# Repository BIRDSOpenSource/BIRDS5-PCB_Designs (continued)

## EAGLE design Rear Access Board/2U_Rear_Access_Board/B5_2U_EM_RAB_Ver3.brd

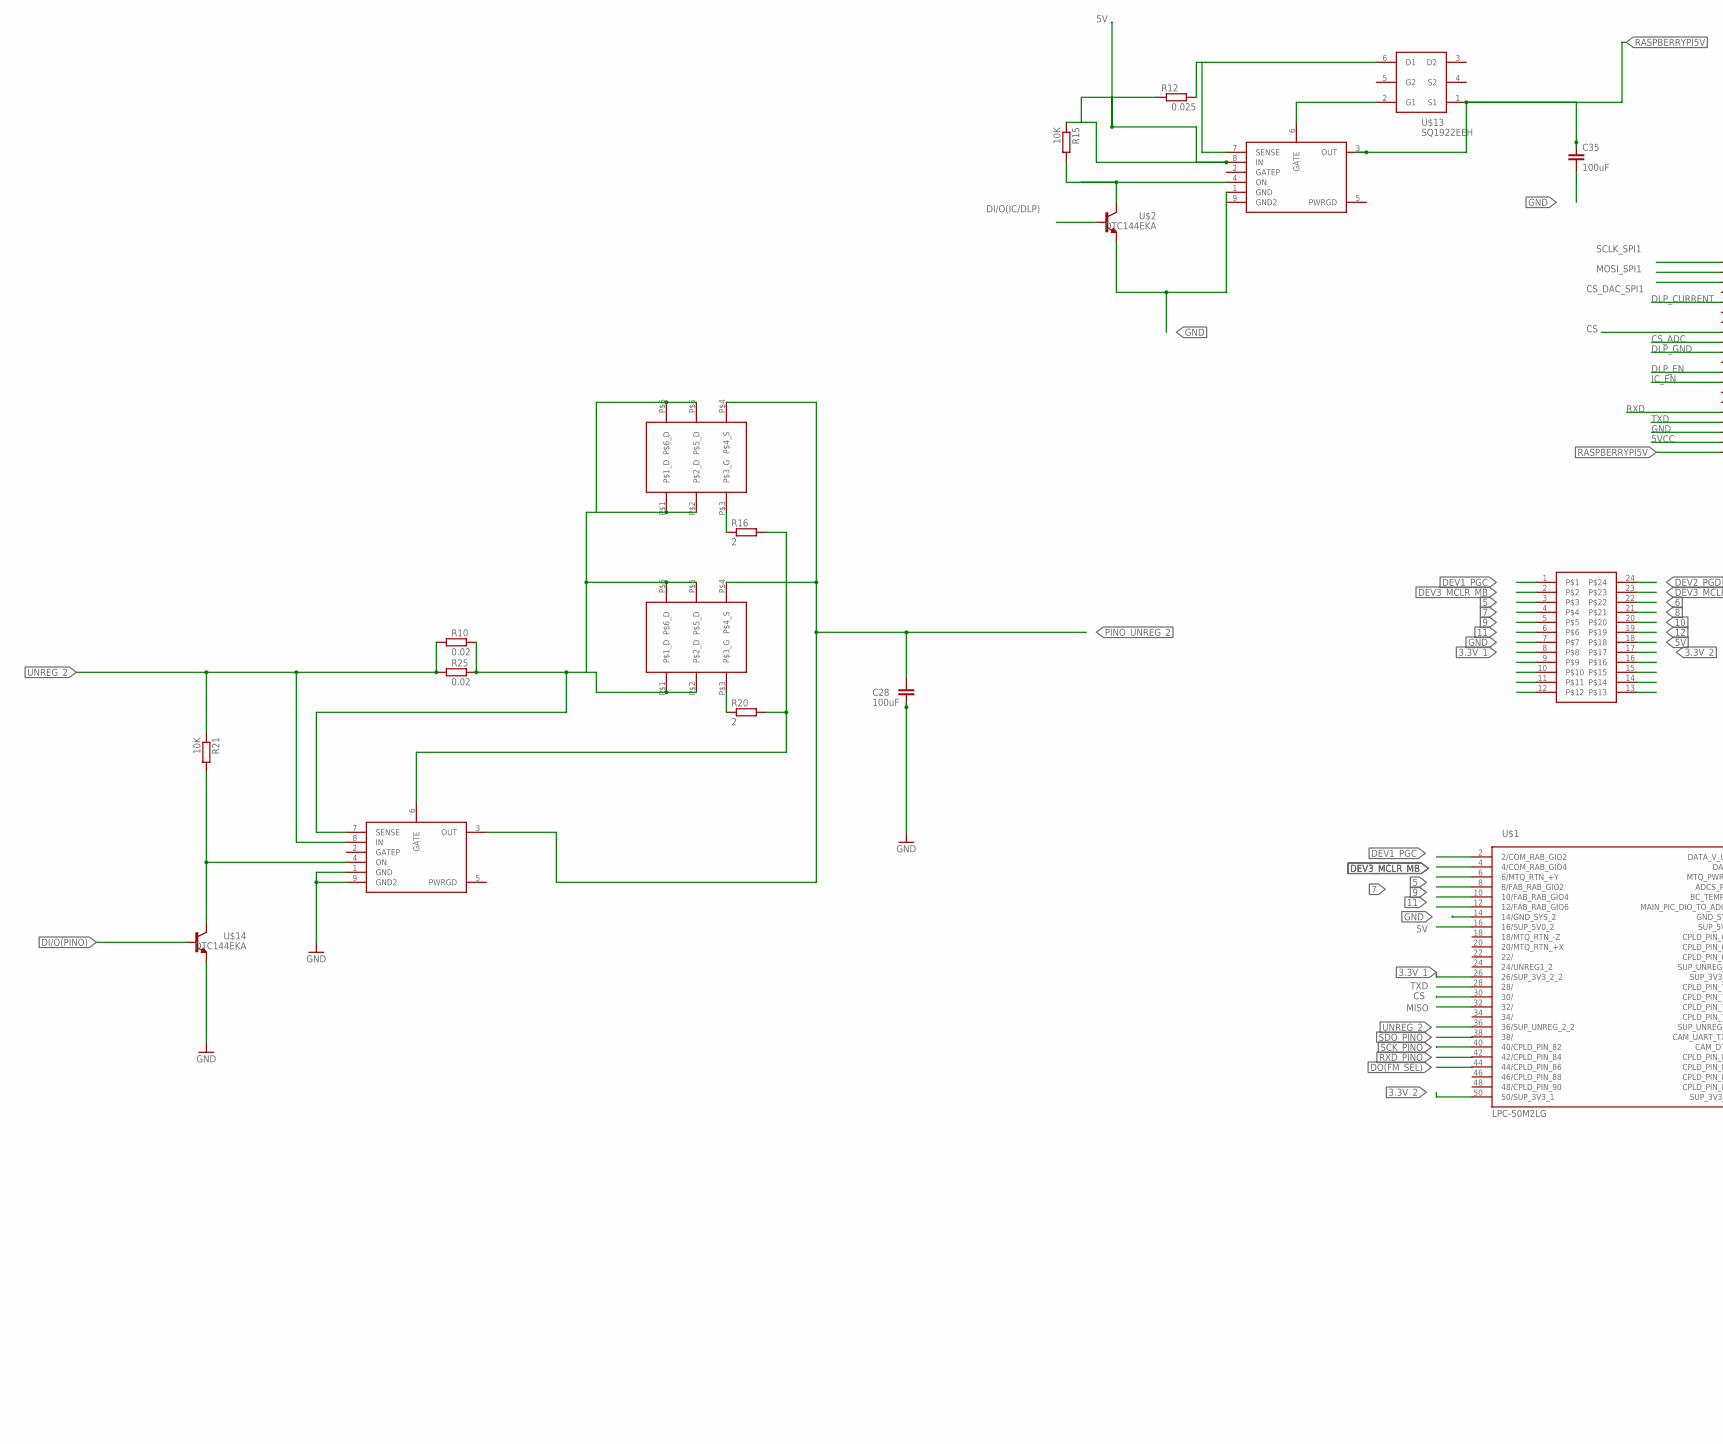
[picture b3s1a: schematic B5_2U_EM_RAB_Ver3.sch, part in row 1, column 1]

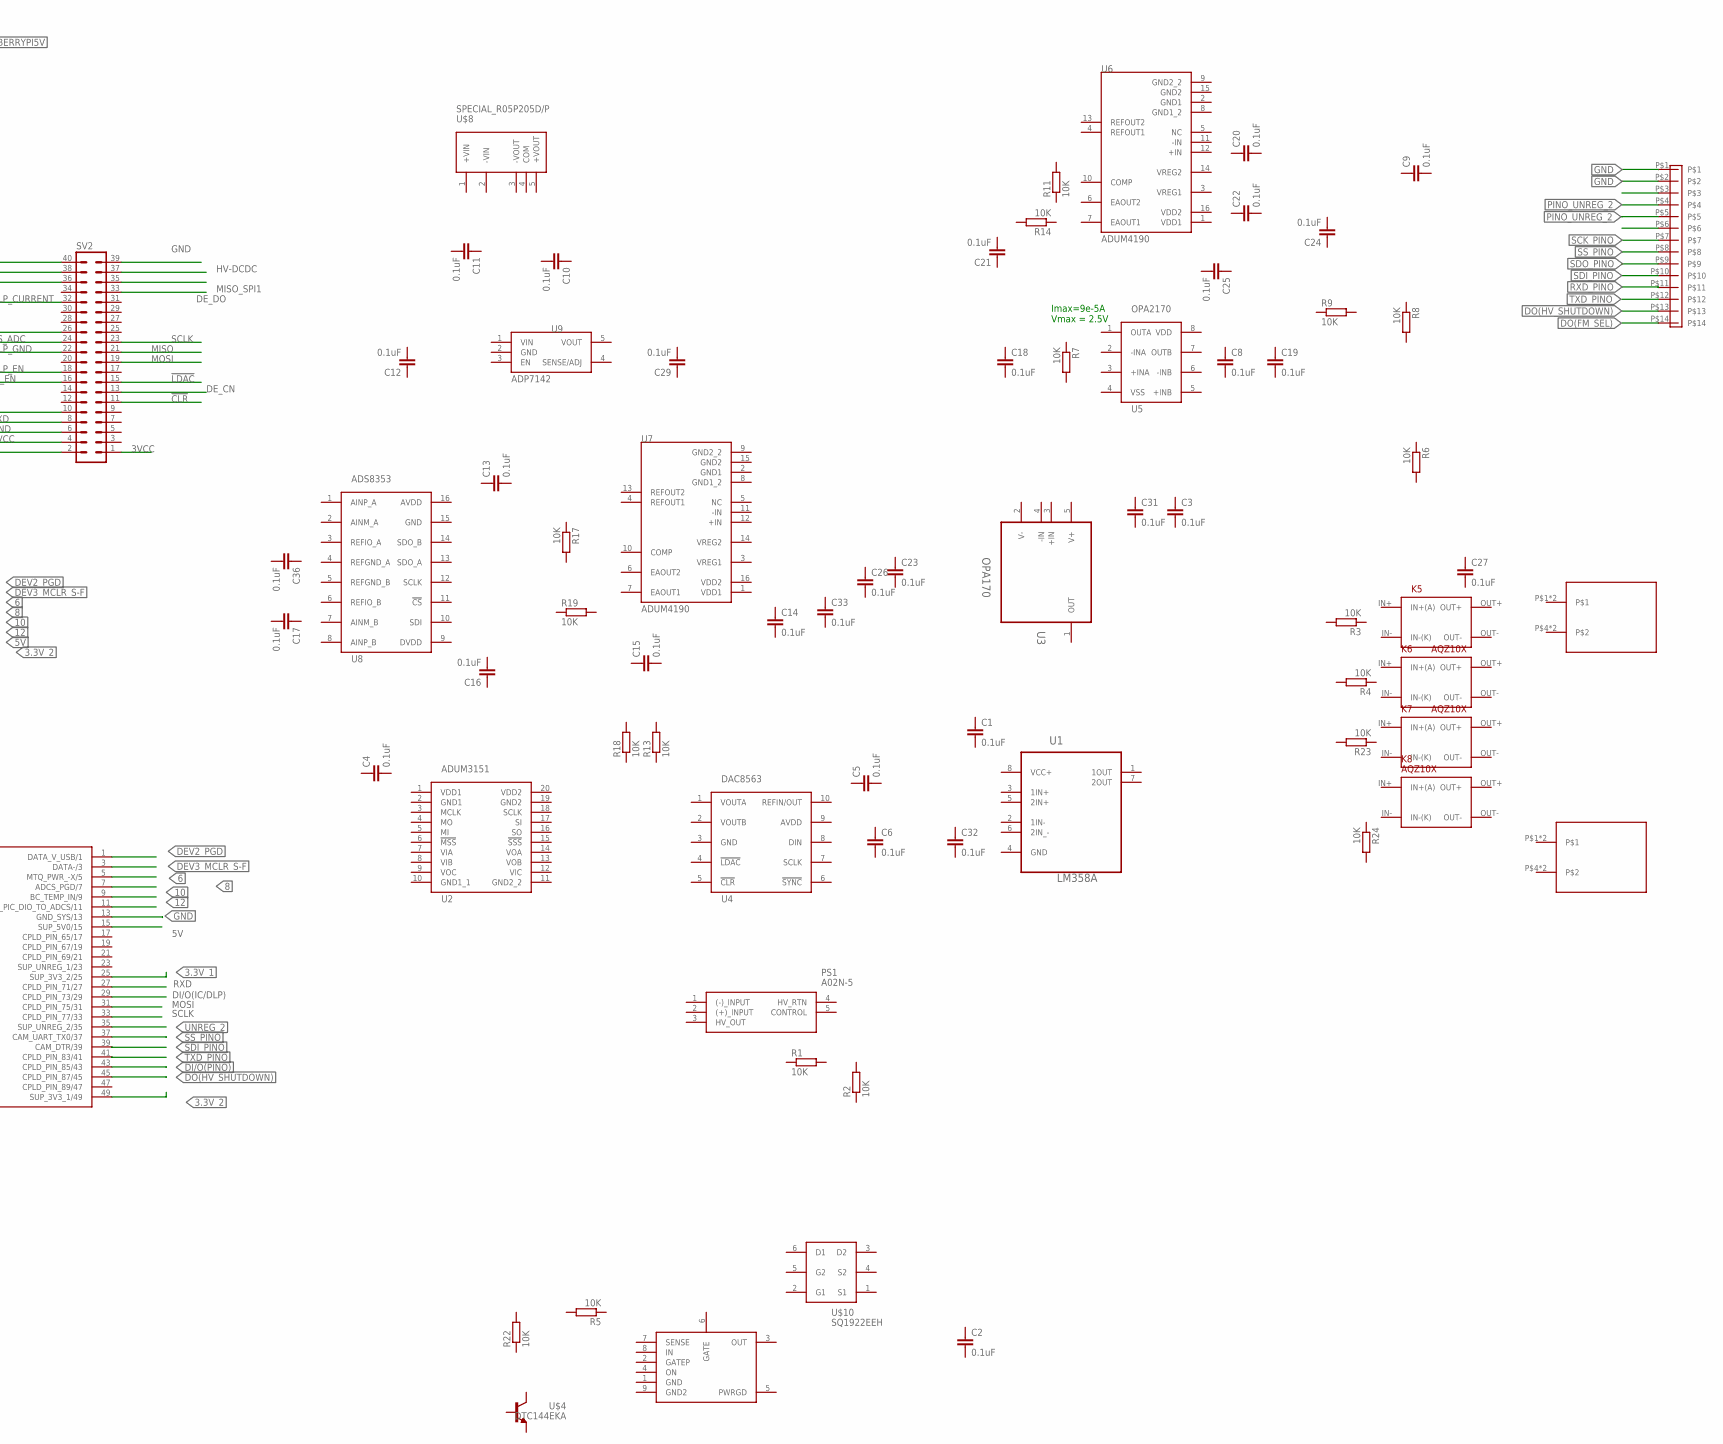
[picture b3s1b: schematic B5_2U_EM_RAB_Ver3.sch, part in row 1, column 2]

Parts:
C1, C2, C3, C4, C5, C6, C8, C9, C10, C11, C12, C13, C14, C15, C16, C17, C18, C19, C20, C21, C22, C23, C24, C25, C26, C27, C29, C31, C32, C33, C36: 0.1uF; C1005
C28: 100uF; C0603
C35: 100uF; C0805
K5, K6, K7, K8: AQZ10X
PS1: A02N-5; A02N5
R1, R2, R3, R4, R5, R6, R7, R8, R9, R11, R13, R14, R15, R17, R18, R19, R21, R22, R23, R24: 10K; R1005
R10, R25: 0.02; R2512
R12: 0.025; R0805
R16, R20: 2; R1005
SV2: MA20-2
U1: LM358A; SOP65P490X110-8N
U2: ADUM3151; SOP65P780X200-20N
U3: OPA170; SOT95P280X145-5N
U4: DAC8563; SOP50P490X110-10N
U5: OPA2170; R-PDSO-G8
U6, U7: ADUM4190; SOIC-16_RI-16-12
U8: ADS8353; SOP65P640X120-16N
U9: ADP7142; SOT95P280X100-5N
U$1: LPC-50M2LG
U$2, U$4, U$14: DTC144EKA; BIRDS3_CAM_MSN_SOT346-R
U$3: RAB_CONECTOR; HDRVR24W40P127_2X12_1564X310X455B
U$5: B14B-PASK-1
U$6, U$11, U$12: BIRDS5_LTC4361
U$7, U$9: DF61_DF61; DF61_DF61Y
U$8: SPECIAL_R05P205D/P
U$10, U$13: SQ1922EEH; BIRDS3_CAM_MSN_SOT65P210X110-6N
U$15, U$16: SSM6K411TU

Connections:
3.3V_1: U$1.25 (SUP_3V3_2/25), U$1.26 (26/SUP_3V3_2_2), U$3.8
3.3V_2: U$1.49 (SUP_3V3_1/49), U$1.50 (50/SUP_3V3_1), U$3.17
3VCC: SV2.1
5: U$1.6 (6/MTQ_RTN_+Y), U$3.3
5V: R12.1, R15.1, U$1.15 (SUP_5V0/15), U$1.16 (16/SUP_5V0_2), U$3.18, U$6.8 (IN)
5VCC: SV2.4
6: U$1.5 (MTQ_PWR_-X/5), U$3.22
7: U$1.8 (8/FAB_RAB_GIO2), U$3.4
8: U$1.7 (ADCS_PGD/7), U$3.21
9: U$1.10 (10/FAB_RAB_GIO4), U$3.5
10: U$1.9 (BC_TEMP_IN/9), U$3.20
11: U$1.12 (12/FAB_RAB_GIO6), U$3.6
12: U$1.11 (MAIN_PIC_DIO_TO_ADCS/11), U$3.19
!CLR: SV2.11
!LDAC: SV2.15
CS: SV2.26, U$1.30 (30/)
CS_ADC: SV2.24
CS_DAC_SPI1: SV2.36
DEV1_PGC: U$1.2 (2/COM_RAB_GIO2), U$3.1
DEV2_PGD: U$1.1 (DATA_V_USB/1), U$3.24
DEV3_MCLR_MB: U$1.4 (4/COM_RAB_GIO4), U$3.2
DEV3_MCLR_S-F: U$1.3 (DATA-/3), U$3.23
DE_CN: SV2.13
DE_DO: SV2.33
DI/O(IC/DLP): U$1.29 (CPLD_PIN_73/29), U$2.2 (B)
DI/O(PINO): U$1.43 (CPLD_PIN_85/43), U$14.2 (B)
DLP_CURRENT: SV2.32
DLP_EN: SV2.18
DLP_GND: SV2.22
DO(FM_SEL): U$1.44 (44/CPLD_PIN_86), U$5.P$14
DO(HV_SHUTDOWN): U$1.45 (CPLD_PIN_87/45), U$5.P$13
GND: C28.2, C35.2, SV2.6, SV2.39, U$1.13 (GND_SYS/13), U$1.14 (14/GND_SYS_2), U$2.1 (E), U$3.7, U$5.P$1, U$5.P$2, U$6.1 (GND), U$6.9 (GND2), U$12.1 (GND), U$12.9 (GND2), U$14.1 (E)
HV-DCDC: SV2.37
IC_EN: SV2.16
MISO: SV2.21, U$1.32 (32/)
MISO_SPI1: SV2.35
MOSI: SV2.19, U$1.31 (CPLD_PIN_75/31)
MOSI_SPI1: SV2.38
unnamed: R20.1, U$15.P$3 (P$3_G)
unnamed: R16.1, U$16.P$3 (P$3_G)
unnamed: R10.2, R25.2, U$12.7 (SENSE), U$15.P$1 (P$1_D), U$15.P$2 (P$2_D), U$15.P$5 (P$5_D), U$15.P$6 (P$6_D), U$16.P$1 (P$1_D), U$16.P$2 (P$2_D), U$16.P$5 (P$5_D), U$16.P$6 (P$6_D)
unnamed: R15.2, U$2.3 (C), U$6.4 (ON)
unnamed: R12.2, U$6.7 (SENSE), U$13.6 (D1)
unnamed: U$6.6 (GATE), U$13.2 (G1)
unnamed: R21.2, U$12.4 (ON), U$14.3 (C)
unnamed: R16.2, R20.2, U$12.6 (GATE)
PINO_UNREG_2: C28.1, U$5.P$4, U$5.P$5, U$12.3 (OUT), U$15.P$4 (P$4_S), U$16.P$4 (P$4_S)
RASPBERRYPI5V: C35.1, SV2.2, U$6.3 (OUT), U$13.1 (S1)
RXD: SV2.10, U$1.27 (CPLD_PIN_71/27)
RXD_PINO: U$1.42 (42/CPLD_PIN_84), U$5.P$11
SCK_PINO: U$1.40 (40/CPLD_PIN_82), U$5.P$7
SCLK: SV2.23, U$1.33 (CPLD_PIN_77/33)
SCLK_SPI1: SV2.40
SDI_PINO: U$1.39 (CAM_DTR/39), U$5.P$10
SDO_PINO: U$1.38 (38/), U$5.P$9
SS_PINO: U$1.37 (CAM_UART_TX0/37), U$5.P$8
TXD: SV2.8, U$1.28 (28/)
TXD_PINO: U$1.41 (CPLD_PIN_83/41), U$5.P$12
UNREG_2: R10.1, R21.1, R25.1, U$1.35 (SUP_UNREG_2/35), U$1.36 (36/SUP_UNREG_2_2), U$12.8 (IN)
V+: U3.5 (V+)
VCC+: U1.8 (VCC+)

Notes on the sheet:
Imax=9e-5A Vmax = 2.5V

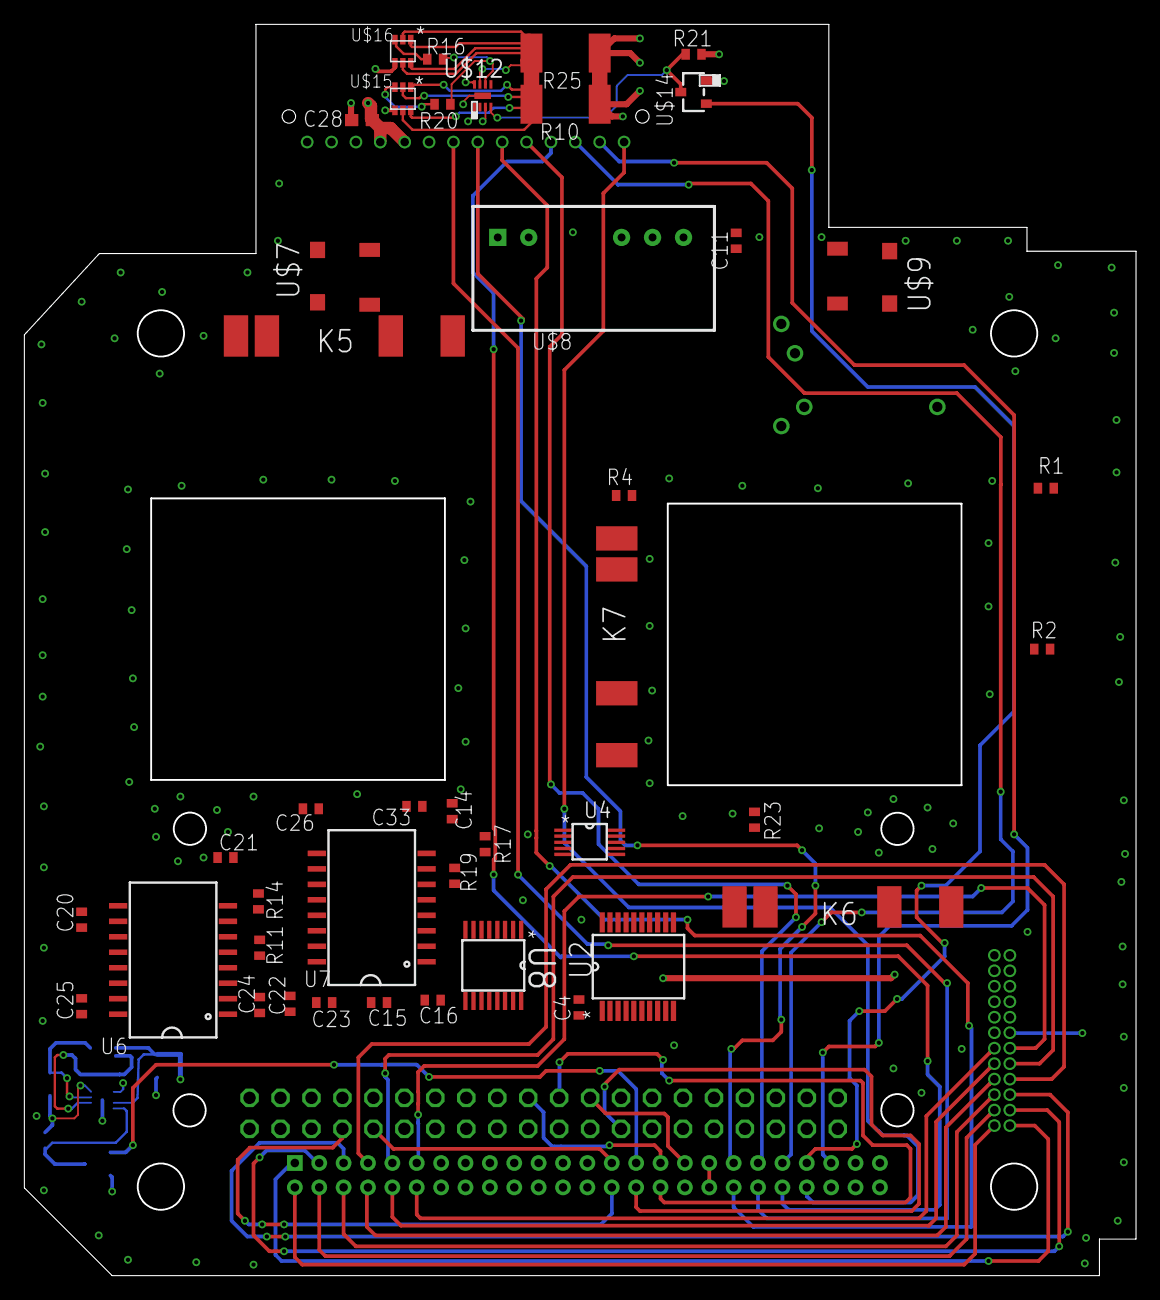
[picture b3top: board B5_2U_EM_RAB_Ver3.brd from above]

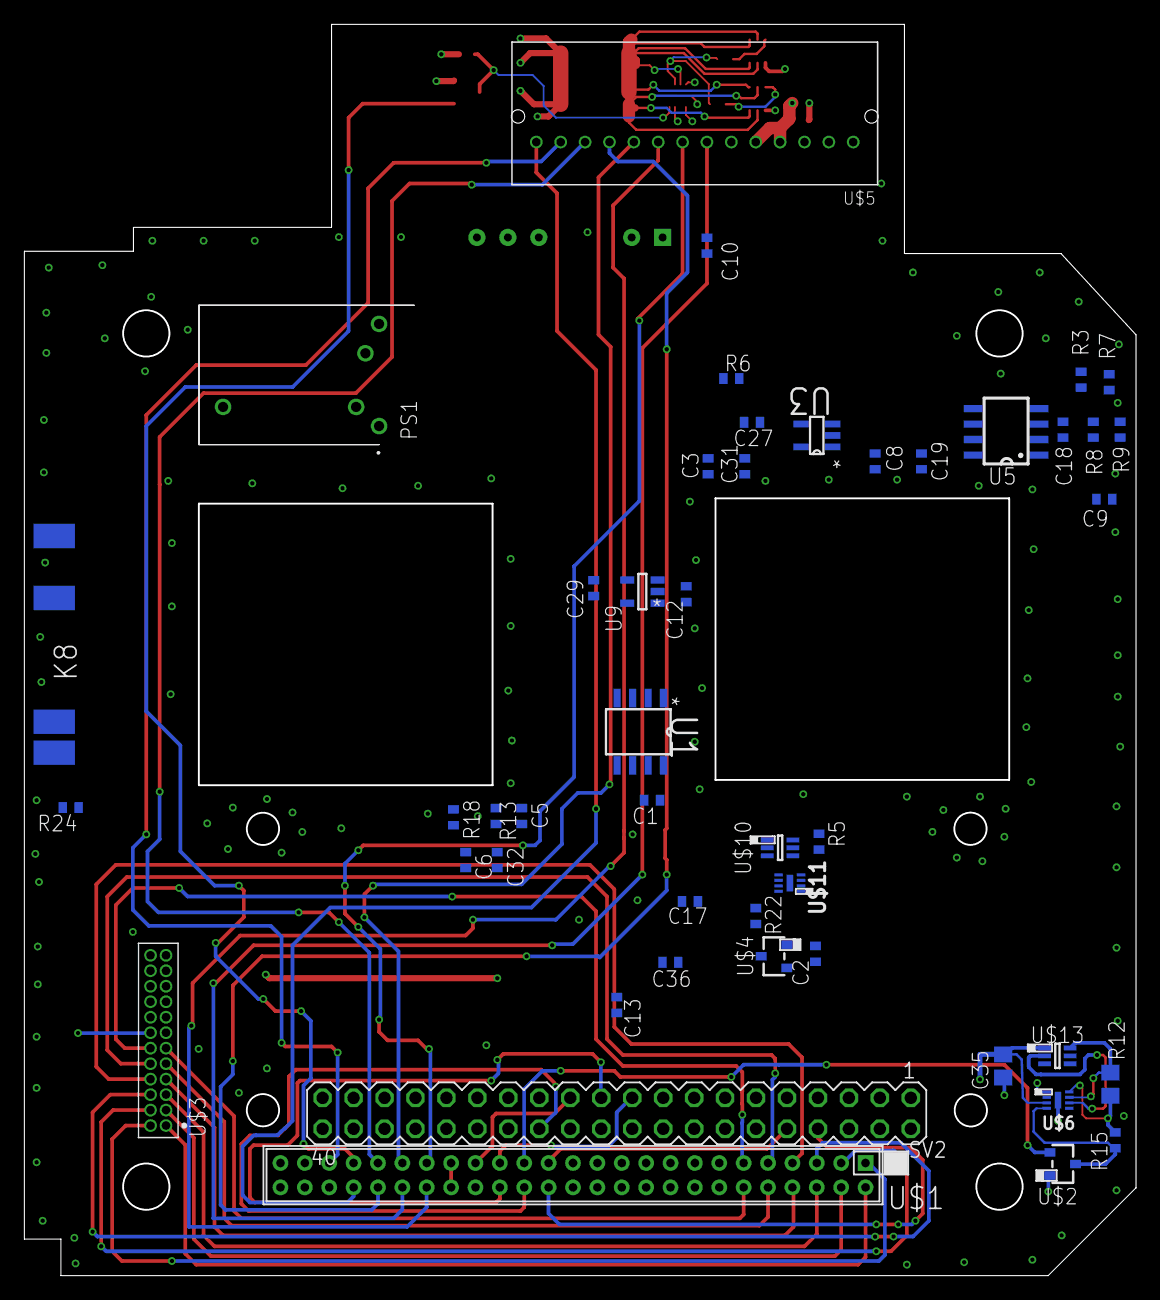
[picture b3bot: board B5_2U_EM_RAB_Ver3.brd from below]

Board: 4 copper layers, 91.2 x 102.7 mm, 89 parts (46 on the bottom side), 43 nets.

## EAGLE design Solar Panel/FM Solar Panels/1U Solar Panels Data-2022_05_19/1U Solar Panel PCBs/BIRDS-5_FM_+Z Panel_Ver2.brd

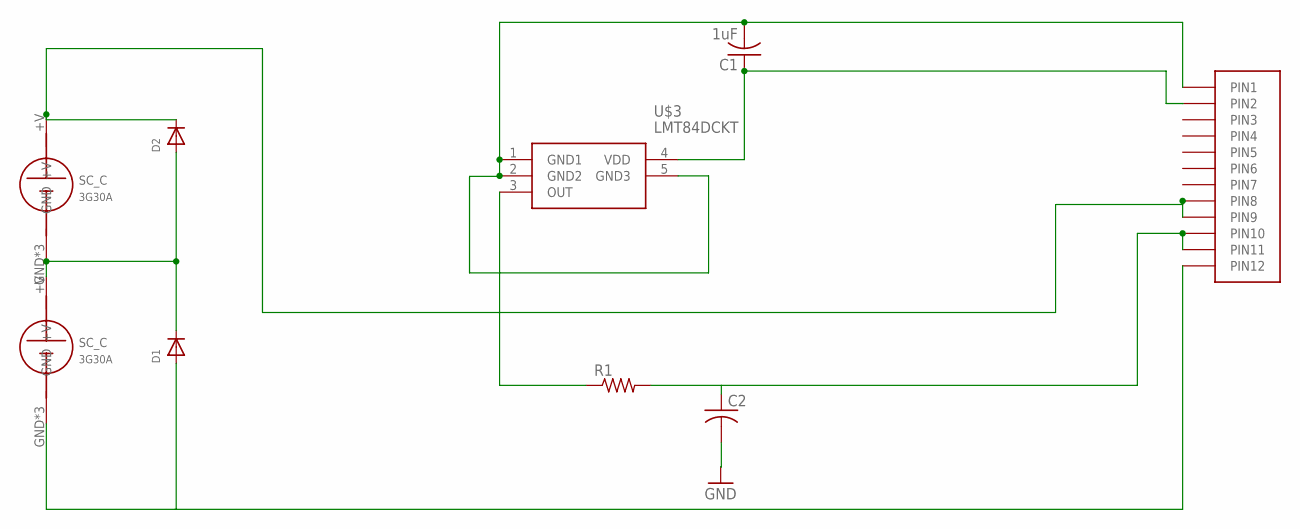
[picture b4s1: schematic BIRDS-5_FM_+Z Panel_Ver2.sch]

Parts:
C1: 1uF; C2012
C2: C-USC2012; C2012
D1, D2: DIODE_SOD-123FL; SOD-123FL
R1: R-US_R0402; R0402
U$1: HEADER12PIN
U$3: LMT84DCKT; SOT65P210X110-5N
U$4, U$5: SC_C

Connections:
+V: D2.C, U$1.P8 (PIN8), U$1.P9 (PIN9), U$4.+V
+VB: D1.C, D2.A, U$4.GND, U$4.GND1 (GND), U$4.GND2 (GND), U$5.+V
GND: C1.2, C2.2, D1.A, U$1.P1 (PIN1), U$1.P12 (PIN12), U$3.1 (GND1), U$3.2 (GND2), U$3.5 (GND3), U$5.GND, U$5.GND1 (GND), U$5.GND2 (GND)
unnamed: C1.1, U$1.P2 (PIN2), U$3.4 (VDD)
unnamed: R1.1, U$3.3 (OUT)
unnamed: C2.1, R1.2, U$1.P10 (PIN10), U$1.P11 (PIN11)

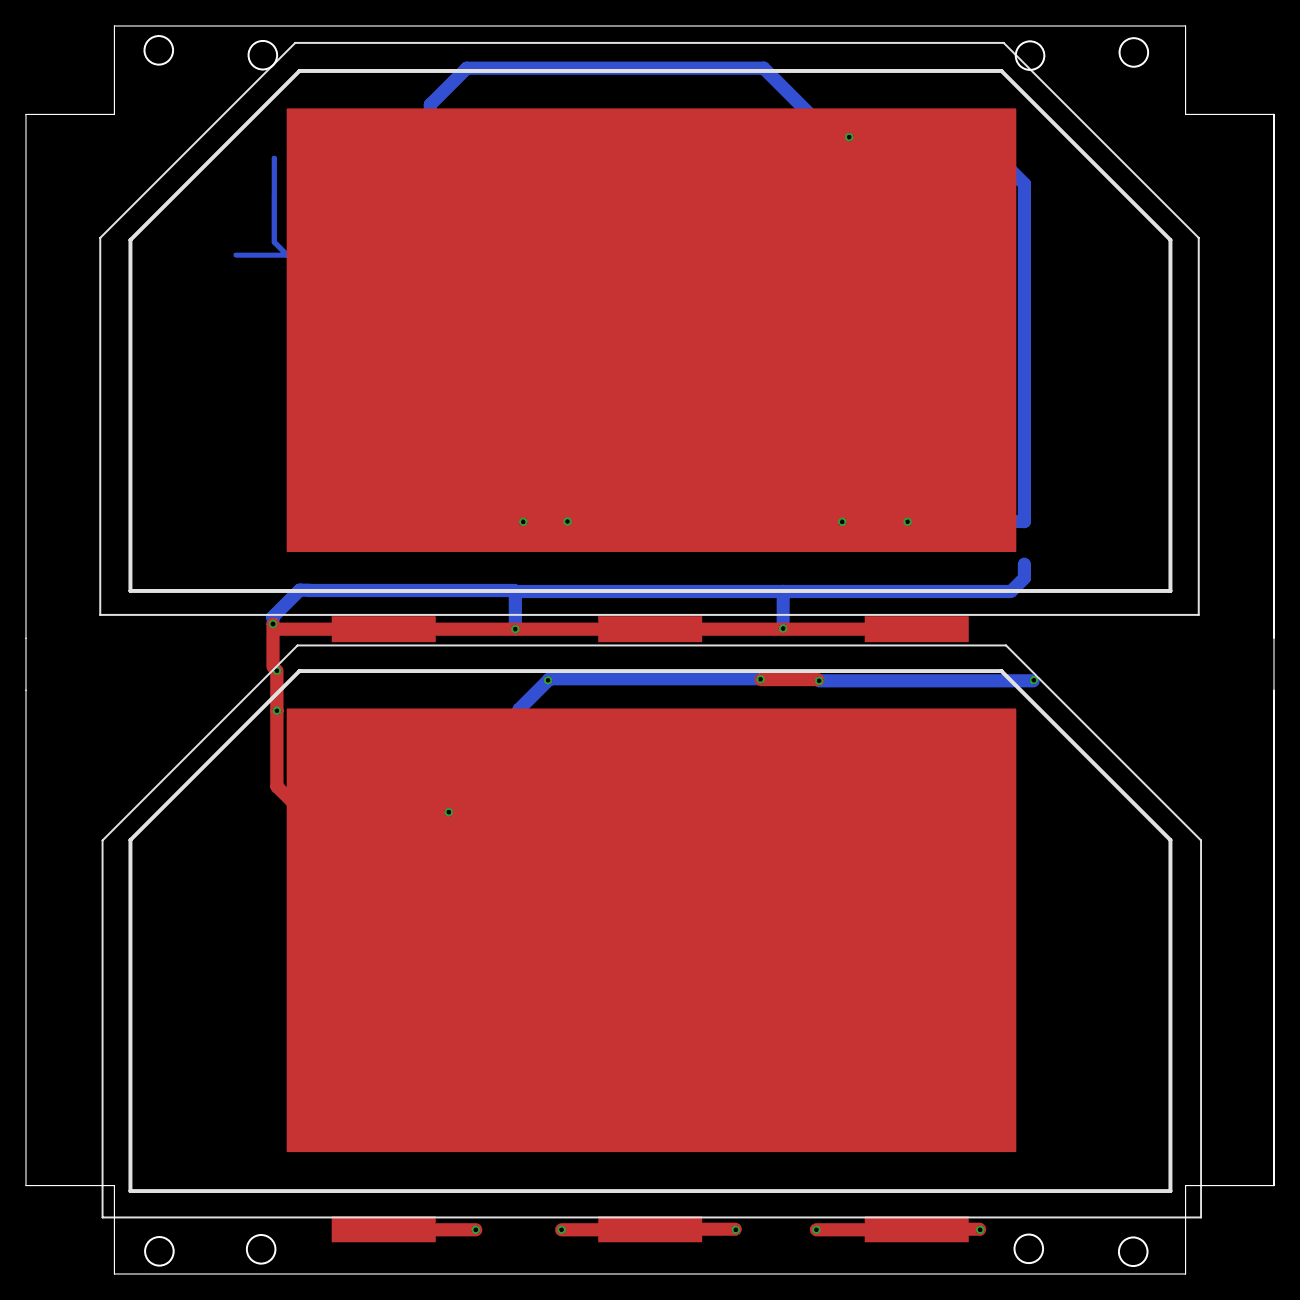
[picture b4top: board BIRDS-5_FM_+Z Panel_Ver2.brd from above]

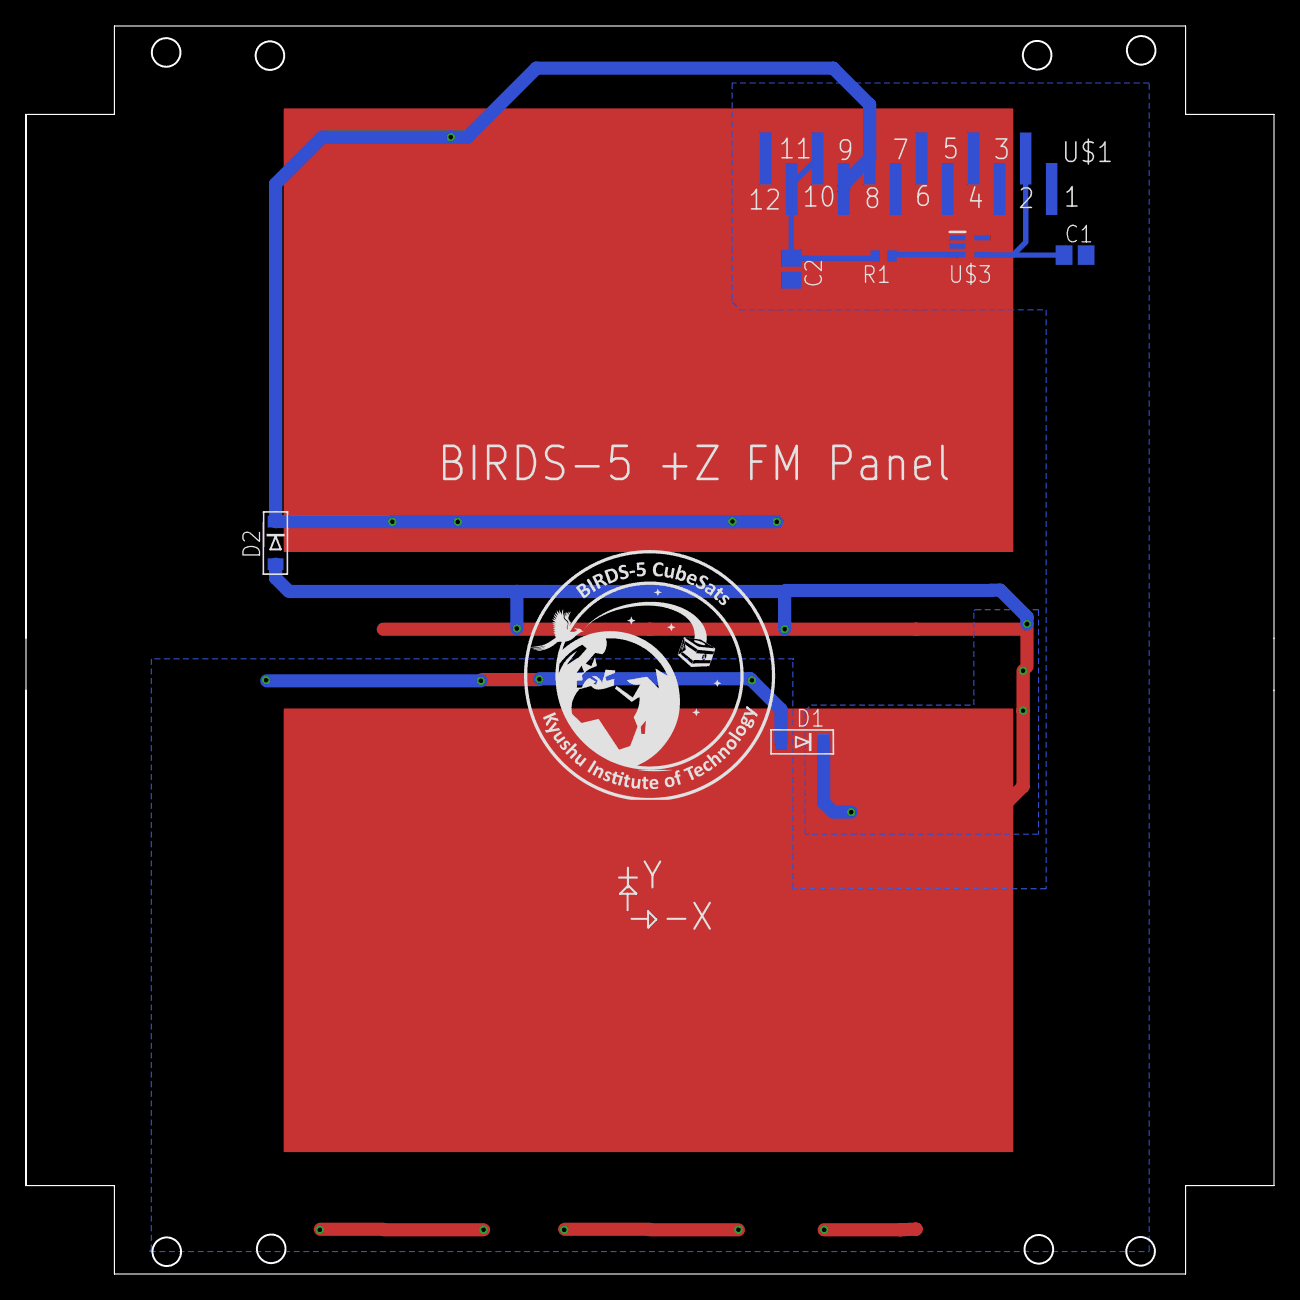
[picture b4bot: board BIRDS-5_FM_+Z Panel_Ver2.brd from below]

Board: 2 copper layers, 96.0 x 96.0 mm, 9 parts (5 on the bottom side), 6 nets.

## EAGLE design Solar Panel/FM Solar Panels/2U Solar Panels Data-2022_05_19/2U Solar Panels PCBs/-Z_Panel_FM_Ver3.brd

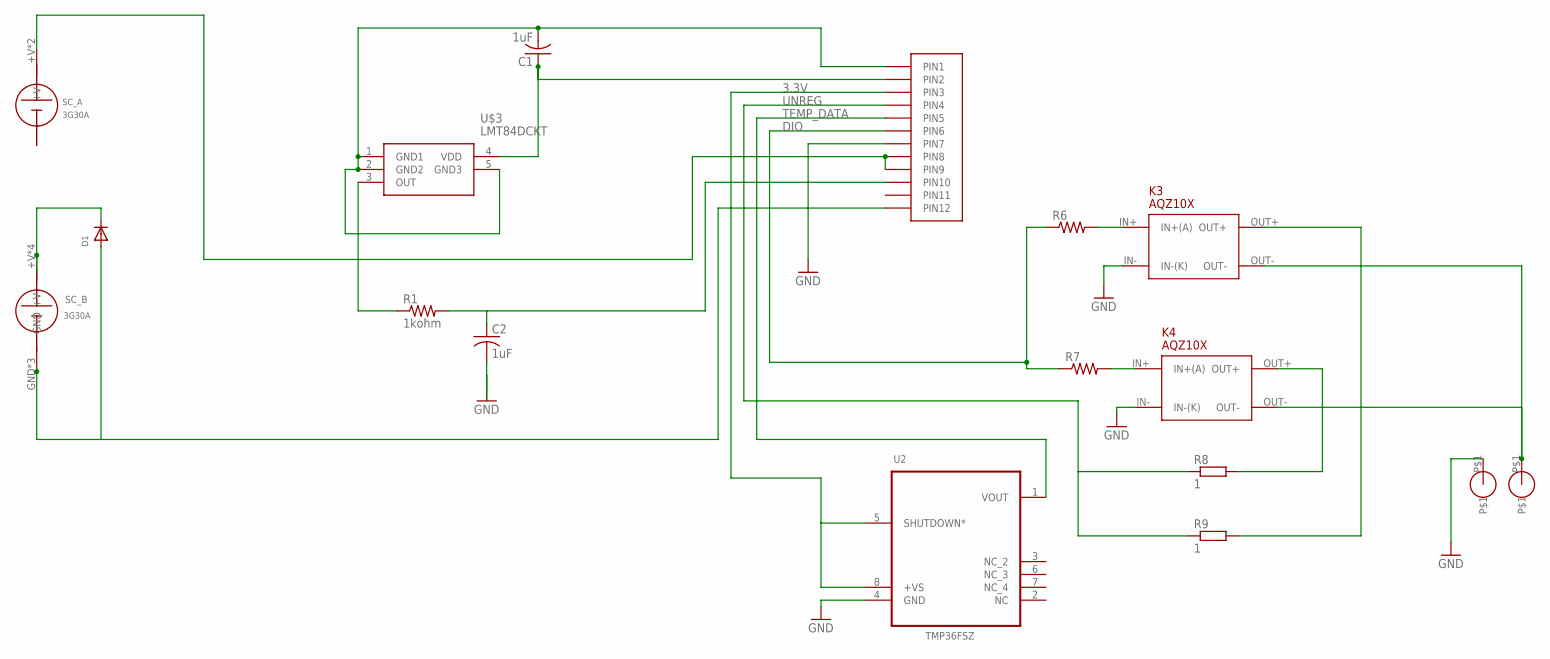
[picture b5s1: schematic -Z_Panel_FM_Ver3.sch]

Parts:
C1, C2: 1uF; C0805
D1: DIODE_SOD-123FL; SOD-123FL
GND9: NICR_HOLE
HOLE1: NICR_HOLE
K3, K4: AQZ10X
R1: 1kohm; R0402
R6, R7: R-US_R0402; R0402
R8, R9: 1; R1218
U2: TMP36FSZ; SOIC_N
U$1: HEADER12PIN
U$3: LMT84DCKT; SOT65P210X110-5N
U$4: SC_A
U$5: SC_B

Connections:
3.3V: U2.5 (SHUTDOWN*), U2.8 (+VS), U$1.P3 (PIN3)
+V: U$1.P8 (PIN8), U$1.P9 (PIN9), U$4.+V, U$4.+V1
+VB: D1.C, U$5.+V, U$5.+V2 (+V), U$5.+V3 (+V), U$5.+V4 (+V)
DIO: R6.1, R7.1, U$1.P6 (PIN6)
GND: C1.2, C2.2, D1.A, GND9.P$1, K3.IN- (IN-(K)), K4.IN- (IN-(K)), U2.4 (GND), U$1.P1 (PIN1), U$1.P7 (PIN7), U$1.P12 (PIN12), U$3.1 (GND1), U$3.2 (GND2), U$3.5 (GND3), U$5.GND, U$5.GND1 (GND), U$5.GND2 (GND)
unnamed: C2.1, R1.2, U$1.P10 (PIN10)
unnamed: C1.1, U$1.P2 (PIN2), U$3.4 (VDD)
unnamed: K3.IN+ (IN+(A)), R6.2
unnamed: K4.IN+ (IN+(A)), R7.2
unnamed: K3.OUT+, R9.2
unnamed: K4.OUT+, R8.2
unnamed: R1.1, U$3.3 (OUT)
unnamed: HOLE1.P$1, K3.OUT-, K4.OUT-
TEMP_DATA: U2.1 (VOUT), U$1.P5 (PIN5)
UNREG: R8.1, R9.1, U$1.P4 (PIN4)

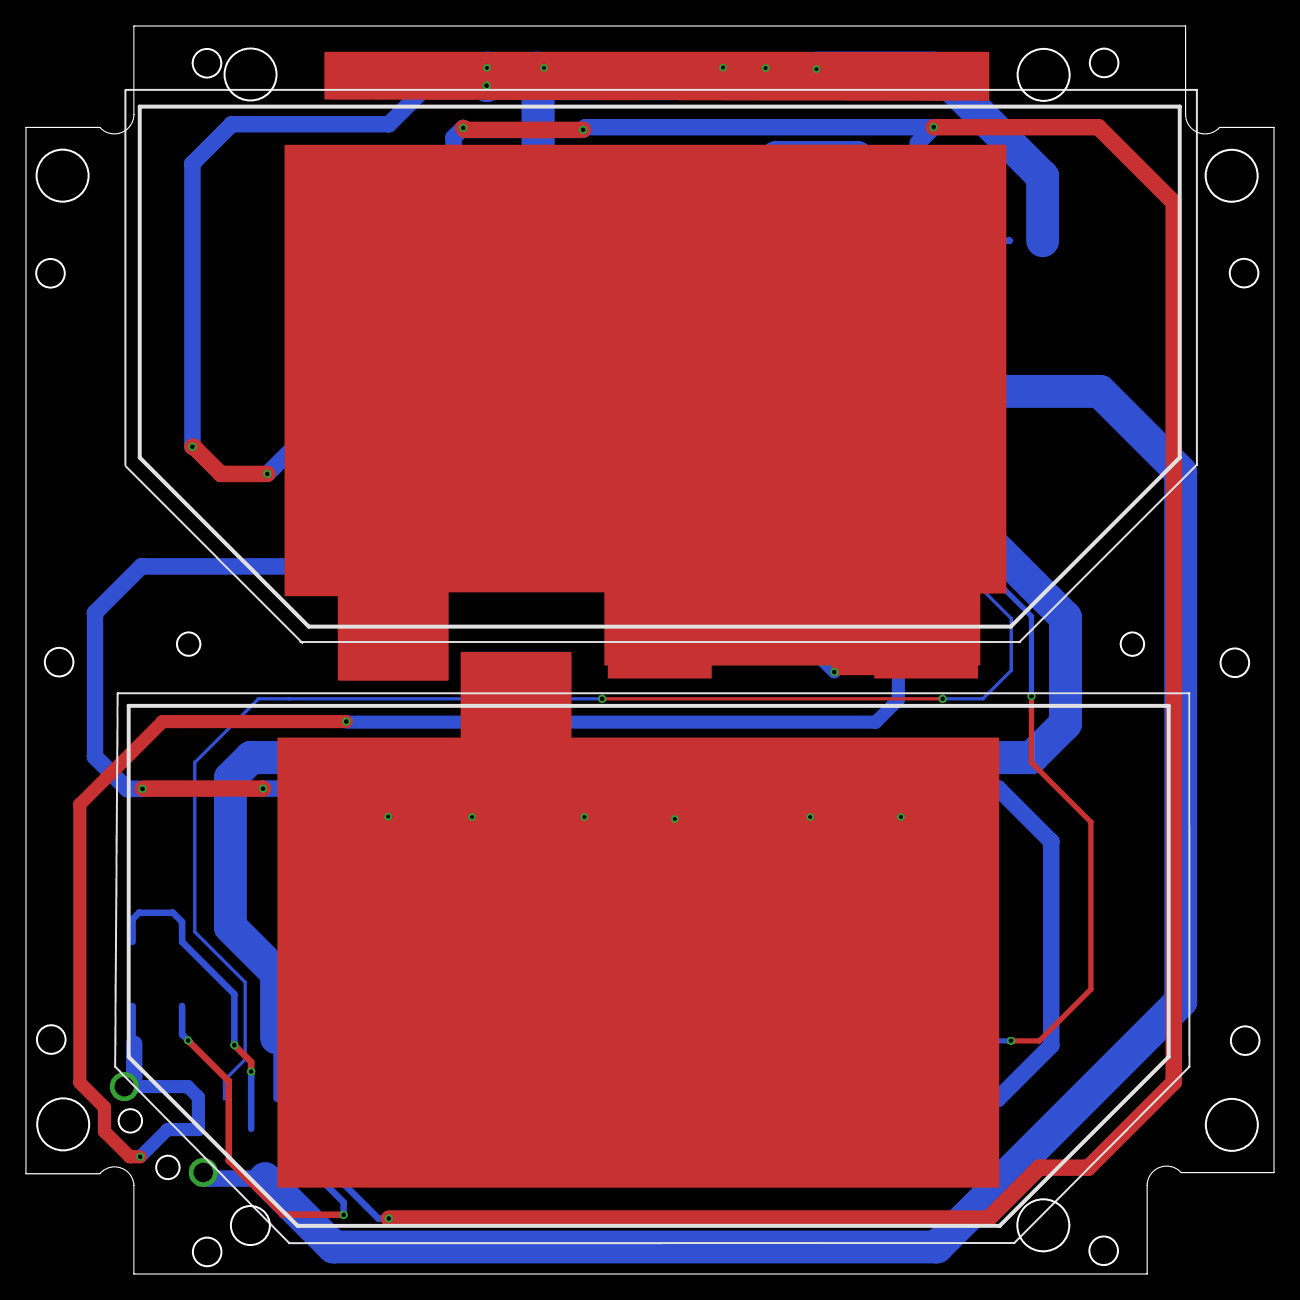
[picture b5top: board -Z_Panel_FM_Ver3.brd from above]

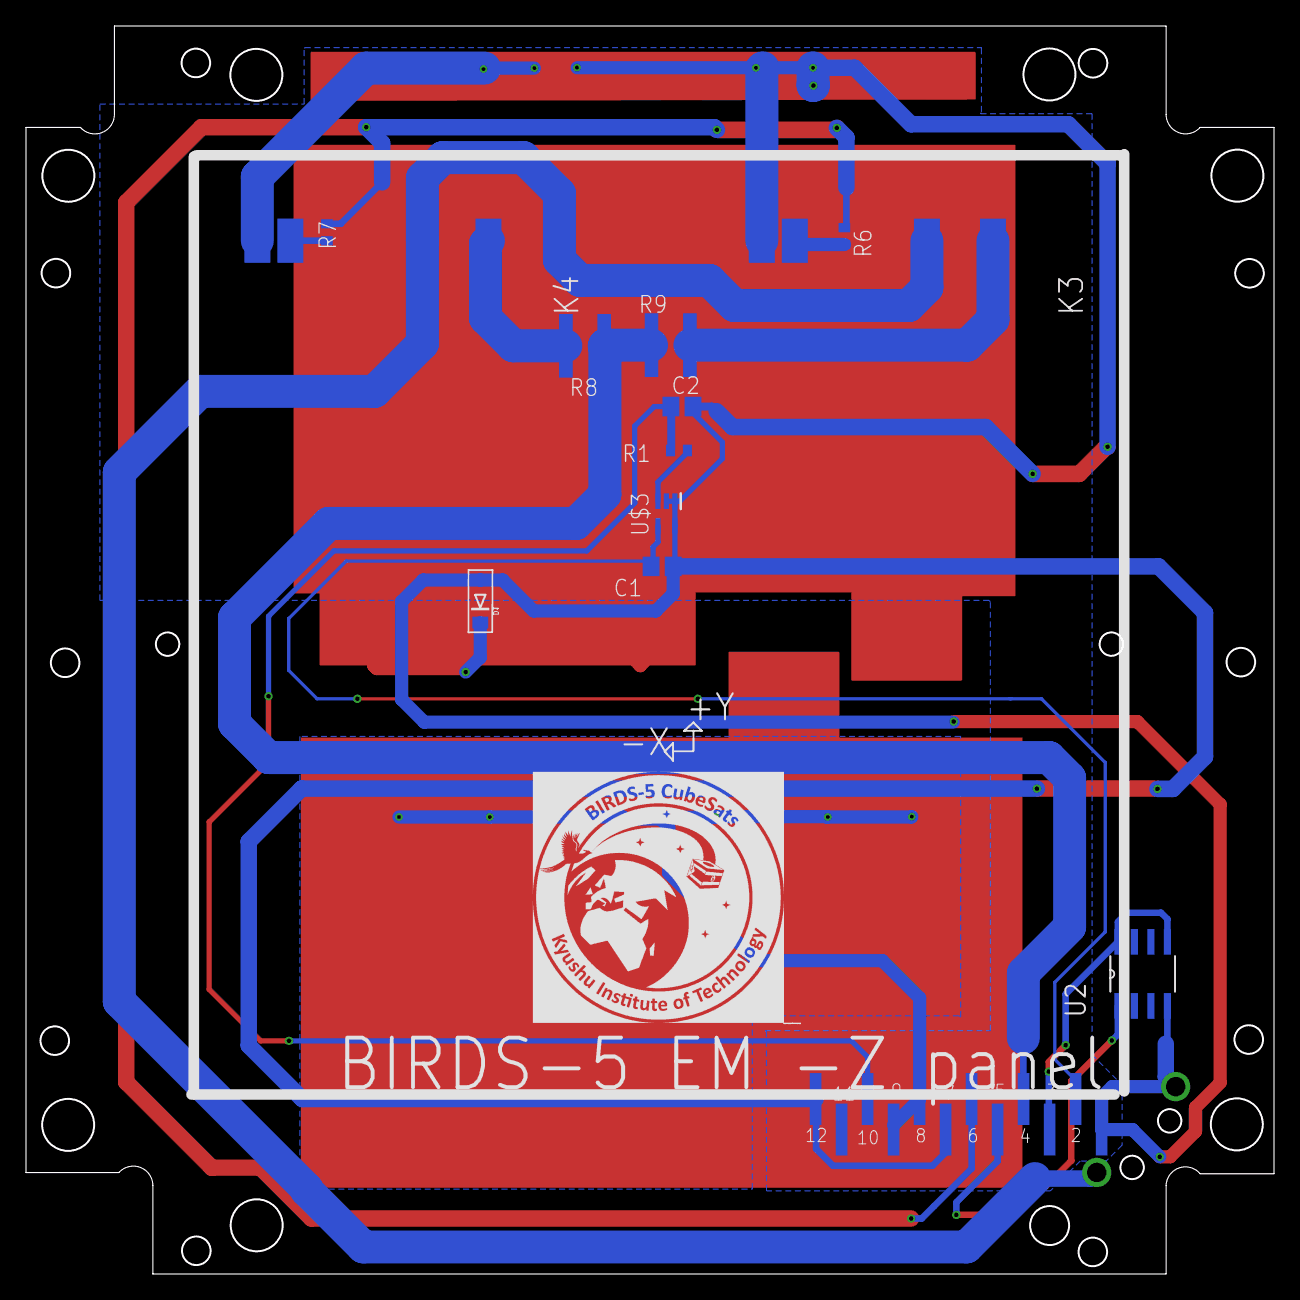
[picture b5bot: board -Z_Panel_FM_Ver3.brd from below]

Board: 2 copper layers, 96.0 x 96.0 mm, 17 parts (12 on the bottom side), 15 nets.

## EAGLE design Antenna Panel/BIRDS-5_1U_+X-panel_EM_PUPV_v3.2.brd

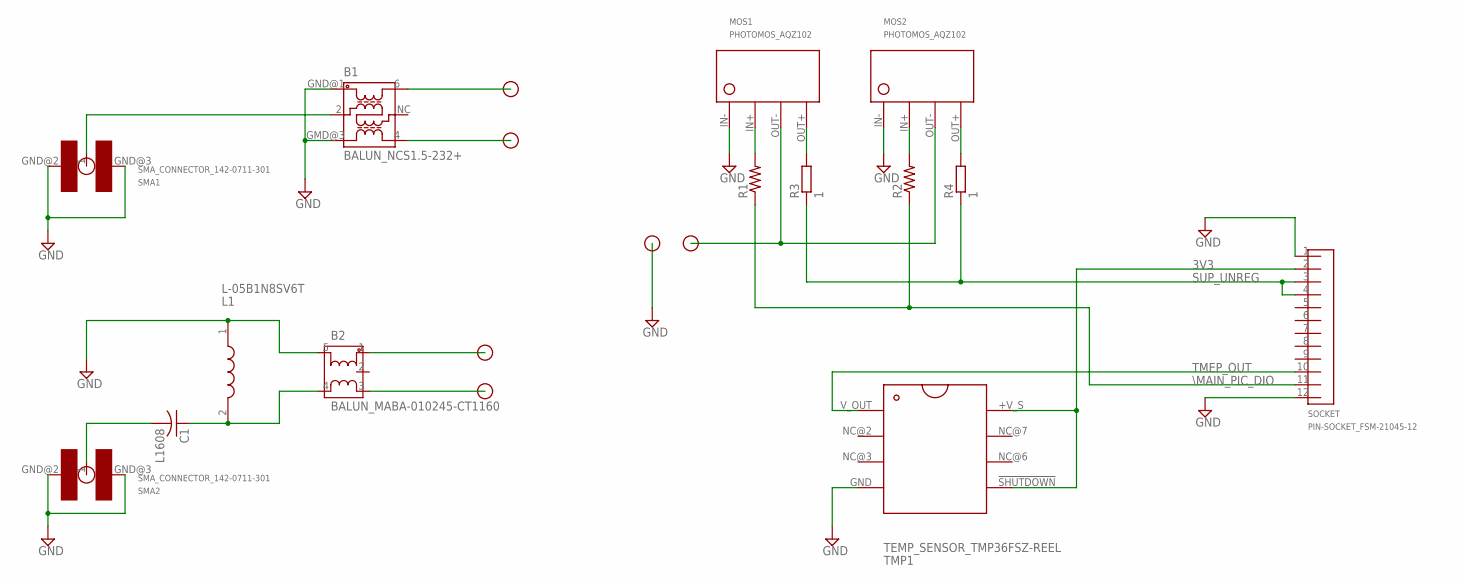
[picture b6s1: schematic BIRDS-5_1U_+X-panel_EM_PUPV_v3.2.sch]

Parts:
B1: BALUN_NCS1.5-232+; NCS1.5-232+
B2: BALUN_MABA-010245-CT1160; MABA-010245-CT1160
C1: L1608
FD1, FD2: FEED_POINT_HEAT_KNIFE
FP1_UHF, FP2_UHF, FP3, FP4: FEED_POINT
L1: L-05B1N8SV6T; INDC0603X33N
MOS1, MOS2: PHOTOMOS_AQZ102; AQZ102
R1, R2: R-US_R0402; R0402
R3, R4: 1; R1218
SMA1, SMA2: SMA_CONNECTOR_142-0711-301; 142-0711-301
SOCKET: PIN-SOCKET_FSM-21045-12
TMP1: TEMP_SENSOR_TMP36FSZ-REEL; TMP36FSZ-REEL

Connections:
3V3: SOCKET.2, TMP1.!SHUTDOWN!, TMP1.+V_S
GND: B1.GMD@3 (GND), B1.GND@1 (GND), B2.5, FD2.FP, L1.1, MOS1.IN-, MOS2.IN-, SMA1.GND@2 (GND), SMA1.GND@3 (GMD), SMA2.GND@2 (GND), SMA2.GND@3 (GMD), SOCKET.1, SOCKET.12, TMP1.GND
unnamed: MOS1.IN+, R1.2
unnamed: MOS2.IN+, R2.2
unnamed: MOS2.OUT+, R4.2
unnamed: MOS1.OUT+, R3.2
unnamed: FD1.FP, MOS1.OUT-, MOS2.OUT-
unnamed: B1.2, SMA1.1
unnamed: C1.2, SMA2.1
unnamed: B2.4, C1.1, L1.2
unnamed: B2.1, FP3.FP
unnamed: B2.3, FP4.FP
unnamed: B1.6, FP1_UHF.FP
unnamed: B1.4, FP2_UHF.FP
SUP_UNREG: R3.1, R4.1, SOCKET.3, SOCKET.4
TMEP_OUT: SOCKET.10, TMP1.V_OUT
\MAIN_PIC_DIO: R1.1, R2.1, SOCKET.11
